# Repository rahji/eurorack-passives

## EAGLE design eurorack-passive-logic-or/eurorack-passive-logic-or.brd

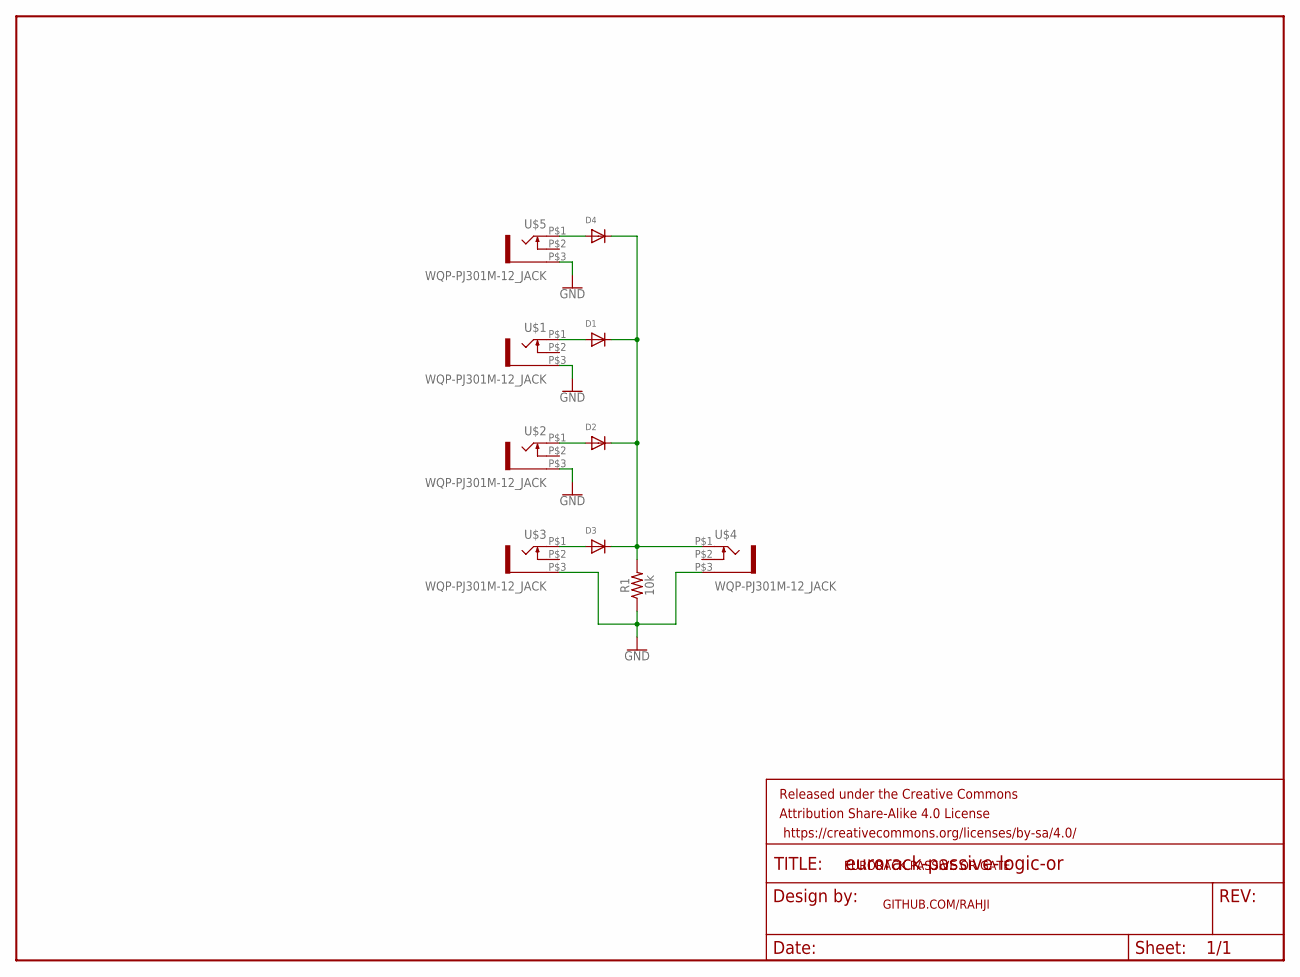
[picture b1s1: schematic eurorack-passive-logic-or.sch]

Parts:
D1, D2, D3, D4: DIODEDO-1N4148; DO-1N4148
FRAME1: FRAME-LETTERNO_PACKAGE; DUMMY
R1: 10k; AXIAL-0.3-KIT
U$1, U$2, U$3, U$4, U$5: WQP-PJ301M-12_JACK

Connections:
GND: R1.P$1 (1), U$1.P$3 (1), U$2.P$3 (1), U$3.P$3 (1), U$4.P$3 (1), U$5.P$3 (1)
unnamed: D1.A, U$1.P$1 (2)
unnamed: D2.A, U$2.P$1 (2)
unnamed: D3.A, U$3.P$1 (2)
unnamed: D4.A, U$5.P$1 (2)
unnamed: D1.C, D2.C, D3.C, D4.C, R1.P$2 (2), U$4.P$1 (2)

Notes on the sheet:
EURORACK PASSIVE OR GATE
GITHUB.COM/RAHJI

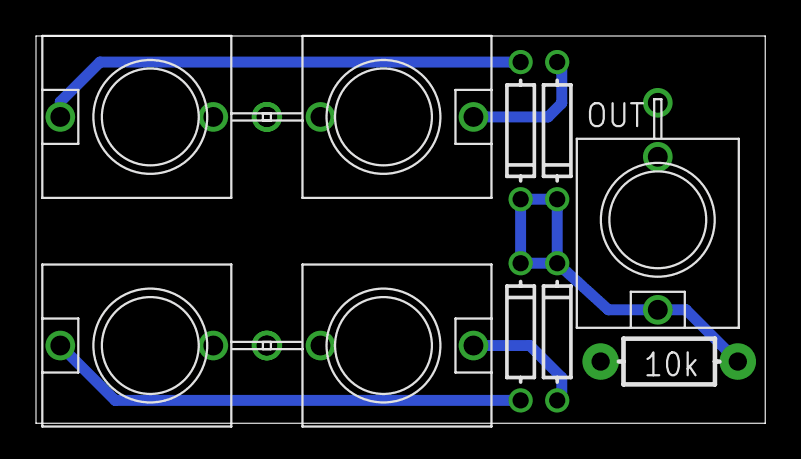
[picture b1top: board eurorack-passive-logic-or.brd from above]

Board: 2 copper layers, 40.5 x 21.5 mm, 11 parts (0 on the bottom side), 6 nets.

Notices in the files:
parts and their libraries:
SparkFun-Resistors: Licensing: Creative Commons ShareAlike 4.0 International - https://creativecommons.org/licenses/by-sa/4.0
SparkFun-Aesthetics: Released under the Creative Commons Attribution Share-Alike 4.0 License
SparkFun-Aesthetics: https://creativecommons.org/licenses/by-sa/4.0
